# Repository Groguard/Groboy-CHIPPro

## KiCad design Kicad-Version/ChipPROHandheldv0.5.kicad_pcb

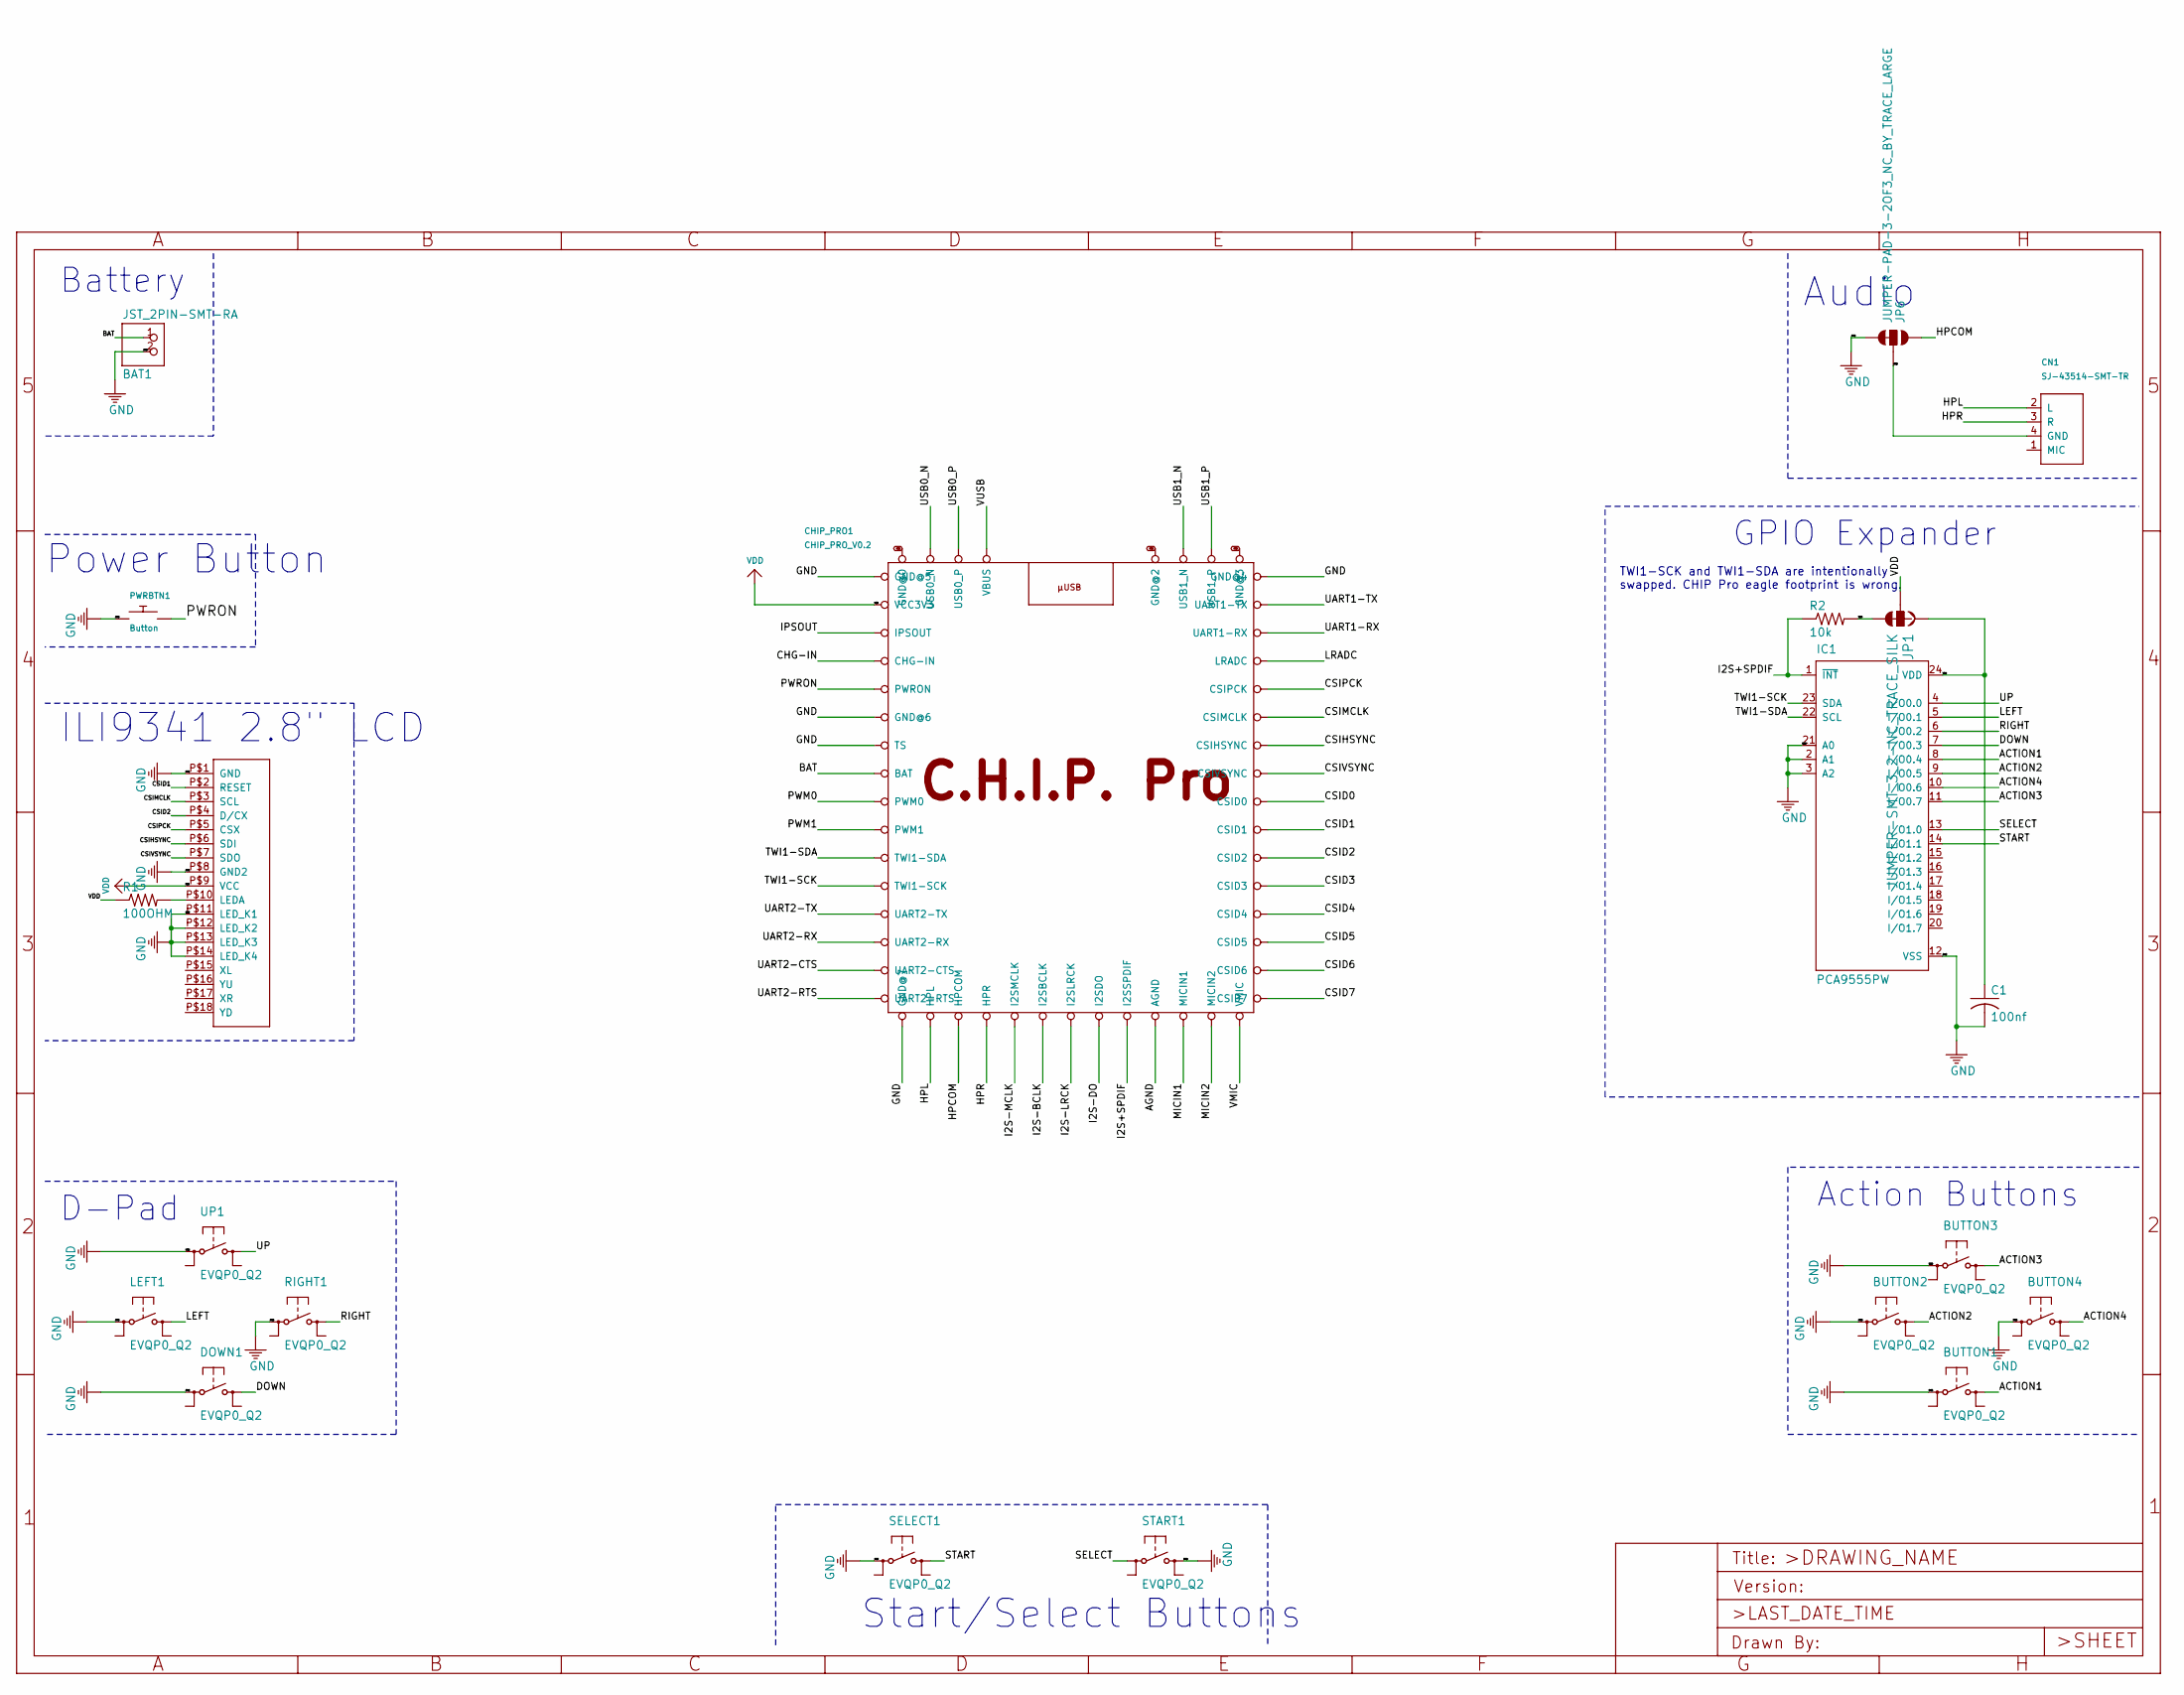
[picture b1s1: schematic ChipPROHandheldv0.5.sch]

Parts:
BAT1: JST_2PIN-SMT-RA; JST-PH-2-SMT-RA
BUTTON1, BUTTON2, BUTTON3, BUTTON4: EVQP0_Q2
C1: 100nf; C0805
CHIP_PRO1: CHIP_PRO_V0.2; GR8_MODULE_V0.2
CN1: SJ-43514-SMT-TR
DOWN1: EVQP0_Q2
IC1: PCA9555PW; TSSOP24
JP1: JUMPER-SMT_3_2-NC_TRACE_SILK; SMT-JUMPER_3_2-NC_TRACE_SILK
JP6: JUMPER-PAD-3-2OF3_NC_BY_TRACE_LARGE; PAD-JUMPER-3-2OF3_NC_BY_TRACE_YES_SILK_LARGE
LEFT1: EVQP0_Q2
PWRBTN1: Button; BTN_CK_KSS
R1: 100OHM; R0805
R2: 10k; R0805
RIGHT1: EVQP0_Q2
SELECT1: EVQP0_Q2
START1: EVQP0_Q2
U$7: ILI9341-2.2; ILI9341
UP1: EVQP0_Q2

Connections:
/ACTION1: BUTTON1.3 (S), IC1.8 (I/O0.4)
/ACTION2: BUTTON2.3 (S), IC1.9 (I/O0.5)
/ACTION3: BUTTON3.3 (S), IC1.11 (I/O0.7)
/ACTION4: BUTTON4.3 (S), IC1.10 (I/O0.6)
/AGND: CHIP_PRO1.AGND
/BAT: BAT1.1 (2), CHIP_PRO1.BAT
/CHG-IN: CHIP_PRO1.CHG-IN
/CSID0: CHIP_PRO1.CSID0
/CSID1: CHIP_PRO1.CSID1, U$7.P$2 (RESET)
/CSID2: CHIP_PRO1.CSID2, U$7.P$4 (D/CX)
/CSID3: CHIP_PRO1.CSID3
/CSID4: CHIP_PRO1.CSID4
/CSID5: CHIP_PRO1.CSID5
/CSID6: CHIP_PRO1.CSID6
/CSID7: CHIP_PRO1.CSID7
/CSIHSYNC: CHIP_PRO1.CSIHSYNC, U$7.P$6 (SDI)
/CSIMCLK: CHIP_PRO1.CSIMCLK, U$7.P$3 (SCL)
/CSIPCK: CHIP_PRO1.CSIPCK, U$7.P$5 (CSX)
/CSIVSYNC: CHIP_PRO1.CSIVSYNC, U$7.P$7 (SDO)
/DOWN: DOWN1.3 (S), IC1.7 (I/O0.3)
/HPCOM: CHIP_PRO1.HPCOM, JP6.1
/HPL: CHIP_PRO1.HPL, CN1.2 (L)
/HPR: CHIP_PRO1.HPR, CN1.3 (R)
/I2S+SPDIF: CHIP_PRO1.I2S+SPDIF (I2SSPDIF), IC1.1 (~INT), R2.1
/I2S-BCLK: CHIP_PRO1.I2S-BCLK (I2SBCLK)
/I2S-DO: CHIP_PRO1.I2S-DO (I2SDO)
/I2S-LRCK: CHIP_PRO1.I2S-LRCK (I2SLRCK)
/I2S-MCLK: CHIP_PRO1.I2S-MCLK (I2SMCLK)
/IPSOUT: CHIP_PRO1.IPSOUT
/LEFT: IC1.5 (I/O0.1), LEFT1.3 (S)
/LRADC: CHIP_PRO1.LRADC
/MICIN1: CHIP_PRO1.MICIN1
/MICIN2: CHIP_PRO1.MICIN2
/PWM0: CHIP_PRO1.PWM0
/PWM1: CHIP_PRO1.PWM1
/PWRON: CHIP_PRO1.PWRON, PWRBTN1.P$2
/RIGHT: IC1.6 (I/O0.2), RIGHT1.3 (S)
/SELECT: IC1.13 (I/O1.0), START1.1
/START: IC1.14 (I/O1.1), SELECT1.3 (S)
/TWI1-SCK: CHIP_PRO1.TWI1-SCK, IC1.23 (SDA)
/TWI1-SDA: CHIP_PRO1.TWI1-SDA, IC1.22 (SCL)
/UART1-RX: CHIP_PRO1.UART1-RX
/UART1-TX: CHIP_PRO1.UART1-TX
/UART2-CTS: CHIP_PRO1.UART2-CTS
/UART2-RTS: CHIP_PRO1.UART2-RTS
/UART2-RX: CHIP_PRO1.UART2-RX
/UART2-TX: CHIP_PRO1.UART2-TX
/UP: IC1.4 (I/O0.0), UP1.3 (S)
/USB0_N: CHIP_PRO1.USB0_N
/USB0_P: CHIP_PRO1.USB0_P
/USB1_N: CHIP_PRO1.USB1_N
/USB1_P: CHIP_PRO1.USB1_P
/VMIC: CHIP_PRO1.VMIC
/VUSB: CHIP_PRO1.VBUS
GND: BAT1.2 (1), BUTTON1.1, BUTTON2.1, BUTTON3.1, BUTTON4.1, C1.2, CHIP_PRO1.GND@0, CHIP_PRO1.GND@1 (GND@2), CHIP_PRO1.GND@2 (GND@3), CHIP_PRO1.GND@3 (GND@4), CHIP_PRO1.GND@4 (GND@5), CHIP_PRO1.GND@6, CHIP_PRO1.GND@7, CHIP_PRO1.TS, CN1.4 (GND), DOWN1.1, IC1.2 (A1), IC1.3 (A2), IC1.12 (VSS), IC1.21 (A0), JP6.2, JP6.3, LEFT1.1, PWRBTN1.P$1, RIGHT1.1, SELECT1.1, START1.3 (S), U$7.P$1 (GND), U$7.P$8 (GND2), U$7.P$11 (LED_K1), U$7.P$12 (LED_K2), U$7.P$13 (LED_K3), U$7.P$14 (LED_K4), UP1.1
unnamed: R1.2, U$7.P$10 (LEDA)
VDD: C1.1, CHIP_PRO1.VCC3V3, IC1.24 (VDD), JP1.1, JP1.2, JP1.3, R1.1, R2.2, U$7.P$9 (VCC)

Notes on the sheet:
Audio
Action Buttons
D-Pad
Battery
Start/Select Buttons
Power Button
ILI9341 2.8" LCD
GPIO Expander
TWI1-SCK and TWI1-SDA are intentionally swapped. CHIP Pro eagle footprint is wrong.

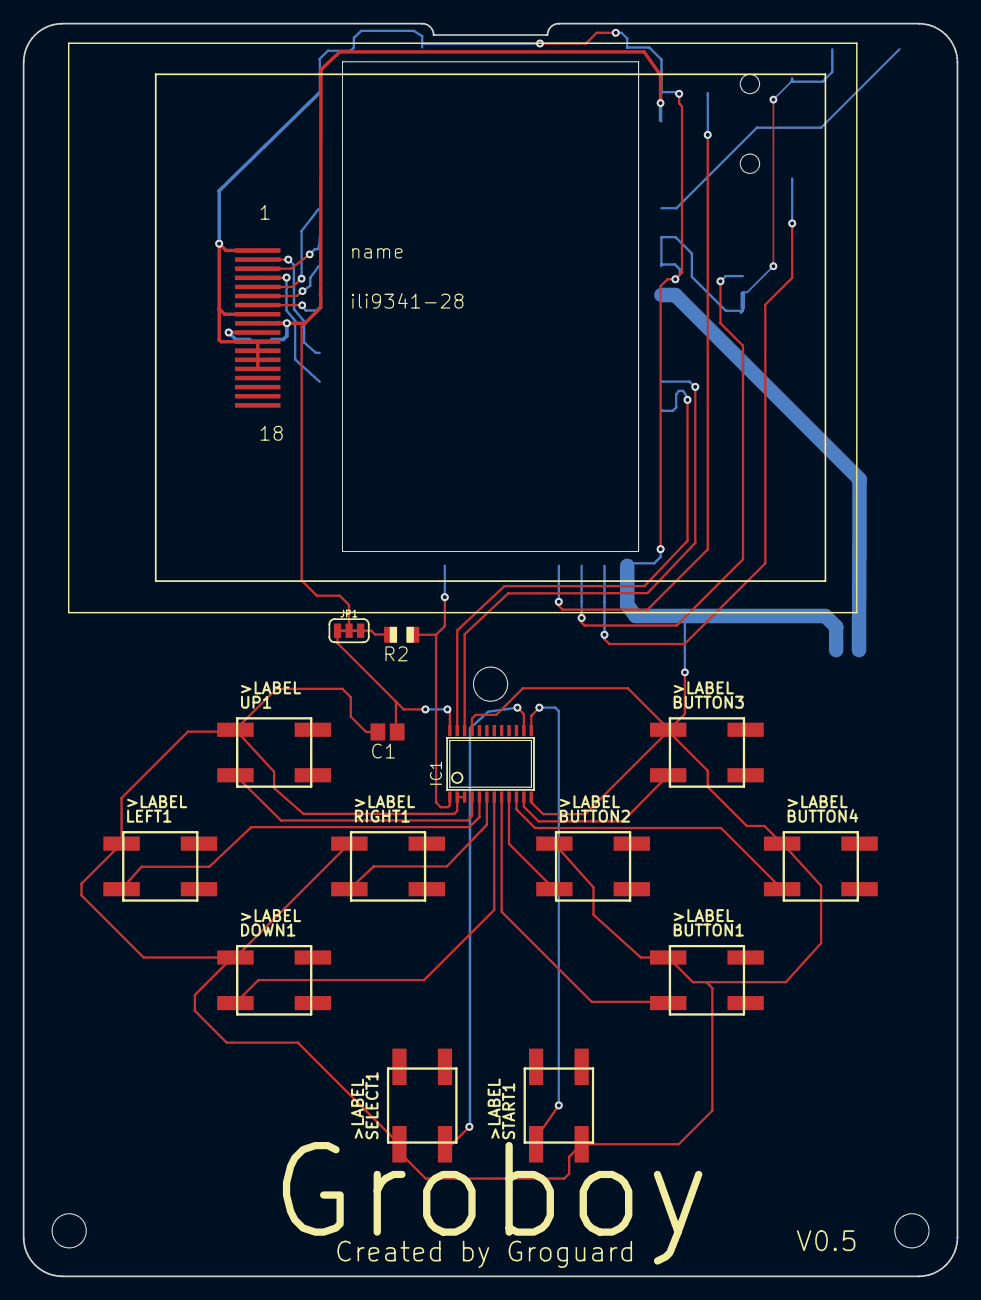
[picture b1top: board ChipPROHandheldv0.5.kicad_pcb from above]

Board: 2 copper layers, 82.0 x 110.0 mm, 24 parts (0 on the bottom side), 27 nets.

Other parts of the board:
@HOLE0, @HOLE1, @HOLE2: (no value)

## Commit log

2020-07-23 First push
2020-07-23 remove empty files
2020-07-23 Reupload newer version
